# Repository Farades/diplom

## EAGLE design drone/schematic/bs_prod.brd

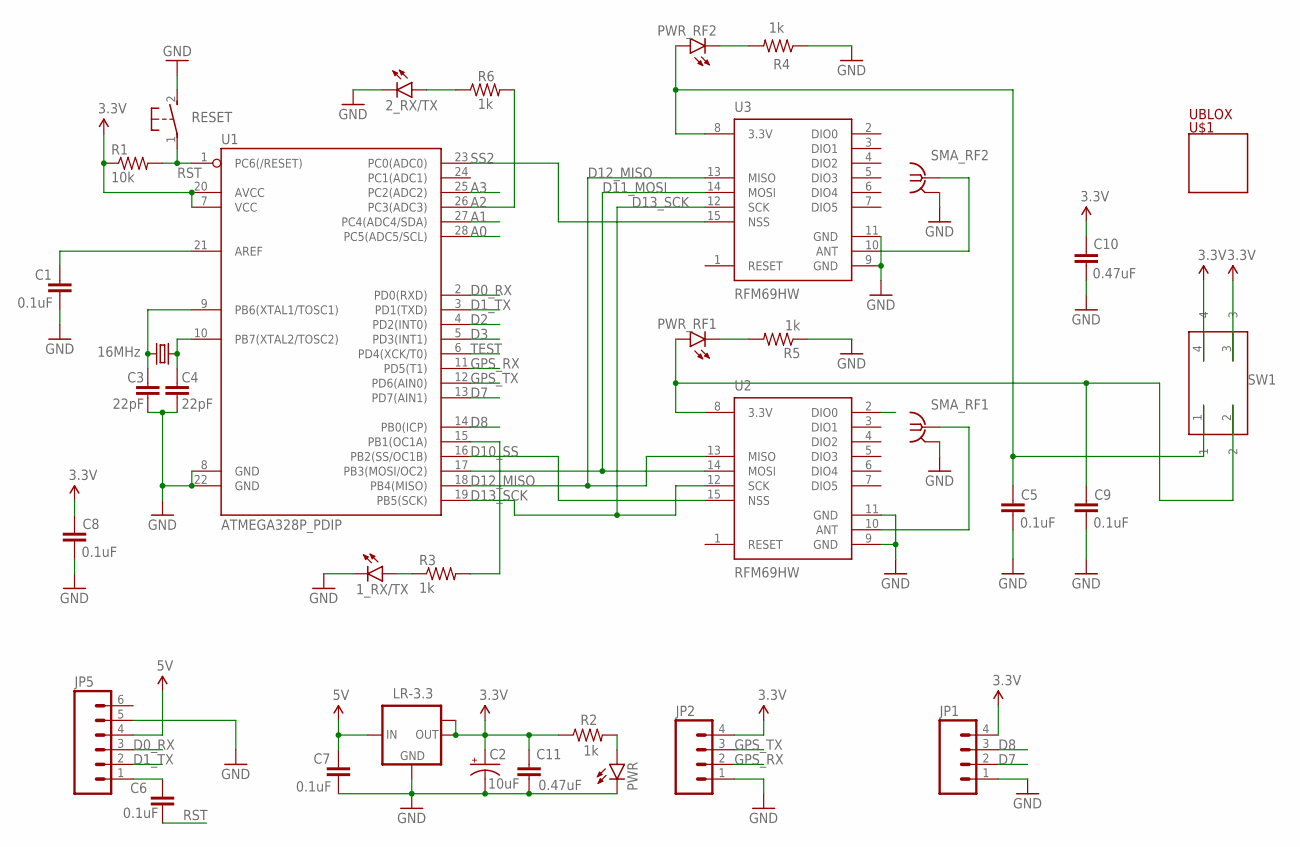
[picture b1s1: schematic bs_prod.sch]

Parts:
1_RX/TX, 2_RX/TX: LED1206; LED-1206
C1, C5, C6, C7, C8, C9: 0.1uF; 1206
C2: 10uF; PANASONIC_C
C3, C4: 22pF; 1206
C10, C11: 0.47uF; 1206
JP1, JP2: M04PTH; 1X04
JP5: M06SIP; 1X06
LR-3.3: LM1117IMPX-3.3; SOT223
PWR: LED1206; LED-1206
PWR_RF1, PWR_RF2: LED1206; LED-1206
R1: 10k; 1206
R2, R3, R4, R5, R6: 1k; 1206
RESET: DTSM-3
SMA_RF1, SMA_RF2: BU-SMC-V
SW1: 418117270902
U1: ATMEGA328P_PDIP; DIL28-3
U2, U3: RFM69HW; RFM69W-XXXS2
U$1: UBLOX
Y1: 16MHz; HC49UP

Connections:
3.3V: C2.+, C8.1, C10.1, C11.1, JP1.4, JP2.4, LR-3.3.2 (OUT), LR-3.3.TAB (OUT1), R1.1, R2.1, SW1.3, SW1.4, U1.7 (VCC), U1.20 (AVCC)
5V: C7.1, JP5.4, LR-3.3.3 (IN)
A0: U1.28 (PC5(ADC5/SCL))
A1: U1.27 (PC4(ADC4/SDA))
A2: R6.2, U1.26 (PC3(ADC3))
A3: U1.25 (PC2(ADC2))
D0_RX: JP5.3, U1.2 (PD0(RXD))
D1_TX: JP5.2, U1.3 (PD1(TXD))
D3: U1.5 (PD3(INT1))
D7: JP1.2, U1.13 (PD7(AIN1))
D8: JP1.3, U1.14 (PB0(ICP))
D10_SS: U1.16 (PB2(SS/OC1B)), U2.15 (NSS)
D11_MOSI: U1.17 (PB3(MOSI/OC2)), U2.14 (MOSI), U3.14 (MOSI)
D12_MISO: U1.18 (PB4(MISO)), U2.13 (MISO), U3.13 (MISO)
D13_SCK: U1.19 (PB5(SCK)), U2.12 (SCK), U3.12 (SCK)
GND: 1_RX/TX.C, 2_RX/TX.C, C1.2, C2.-, C3.2, C4.2, C5.2, C7.2, C8.2, C9.2, C10.2, C11.2, JP1.1, JP2.1, JP5.5, LR-3.3.1 (GND), PWR.C, R4.1, R5.1, RESET.2, SMA_RF1.2, SMA_RF1.3 (2), SMA_RF1.4 (2), SMA_RF1.5 (2), SMA_RF2.2, SMA_RF2.3 (2), SMA_RF2.4 (2), SMA_RF2.5 (2), U1.8 (GND), U1.22 (GND), U2.9 (GND), U2.11 (GND), U3.9 (GND), U3.11 (GND)
GPS_RX: JP2.2, U1.11 (PD5(T1))
GPS_TX: JP2.3, U1.12 (PD6(AIN0))
unnamed: PWR.A, R2.2
unnamed: C3.1, U1.9 (PB6(XTAL1/TOSC1)), Y1.2
unnamed: C4.1, U1.10 (PB7(XTAL2/TOSC2)), Y1.1
unnamed: SMA_RF1.1, U2.10 (ANT)
unnamed: PWR_RF2.C, R4.2
unnamed: C6.1, JP5.1
unnamed: 1_RX/TX.A, R3.1
unnamed: 2_RX/TX.A, R6.1
unnamed: C1.1, U1.21 (AREF)
unnamed: R3.2, U1.15 (PB1(OC1A))
unnamed: C5.1, PWR_RF2.A, SW1.1, U3.8 (3.3V)
unnamed: PWR_RF1.C, R5.2
unnamed: C9.1, PWR_RF1.A, SW1.2, U2.8 (3.3V)
unnamed: SMA_RF2.1, U3.10 (ANT)
RST: C6.2, R1.2, RESET.1, U1.1 (PC6(/RESET))
SS2: U1.23 (PC0(ADC0)), U3.15 (NSS)
TEST: U1.6 (PD4(XCK/T0))

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
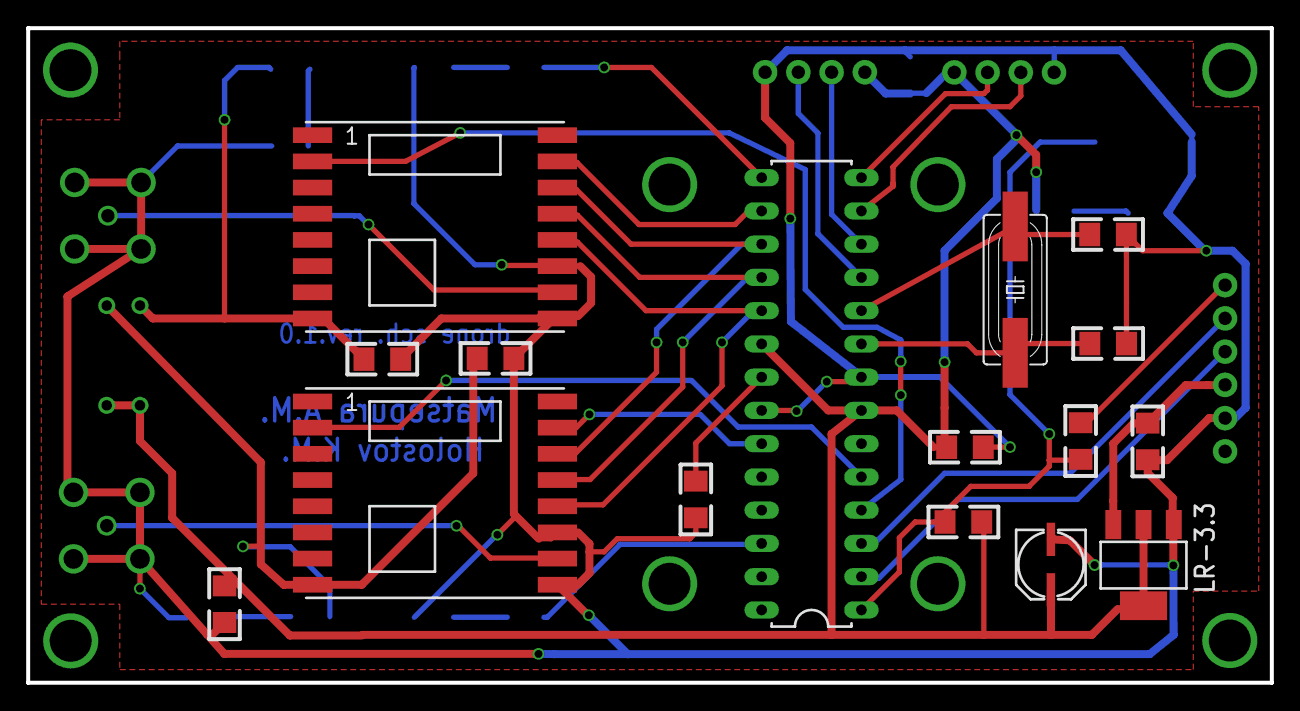
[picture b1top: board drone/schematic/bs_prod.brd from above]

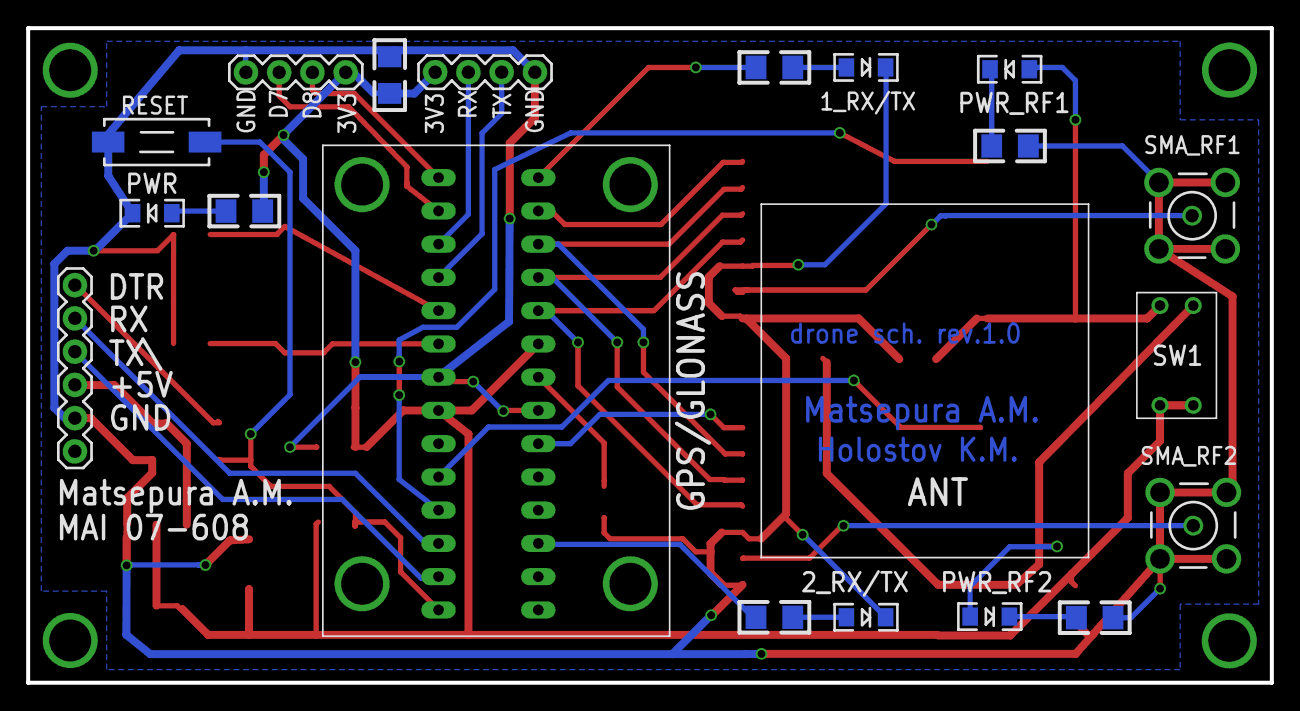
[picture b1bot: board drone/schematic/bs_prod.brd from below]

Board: 2 copper layers, 95.0 x 50.0 mm, 35 parts (19 on the bottom side), 31 nets.

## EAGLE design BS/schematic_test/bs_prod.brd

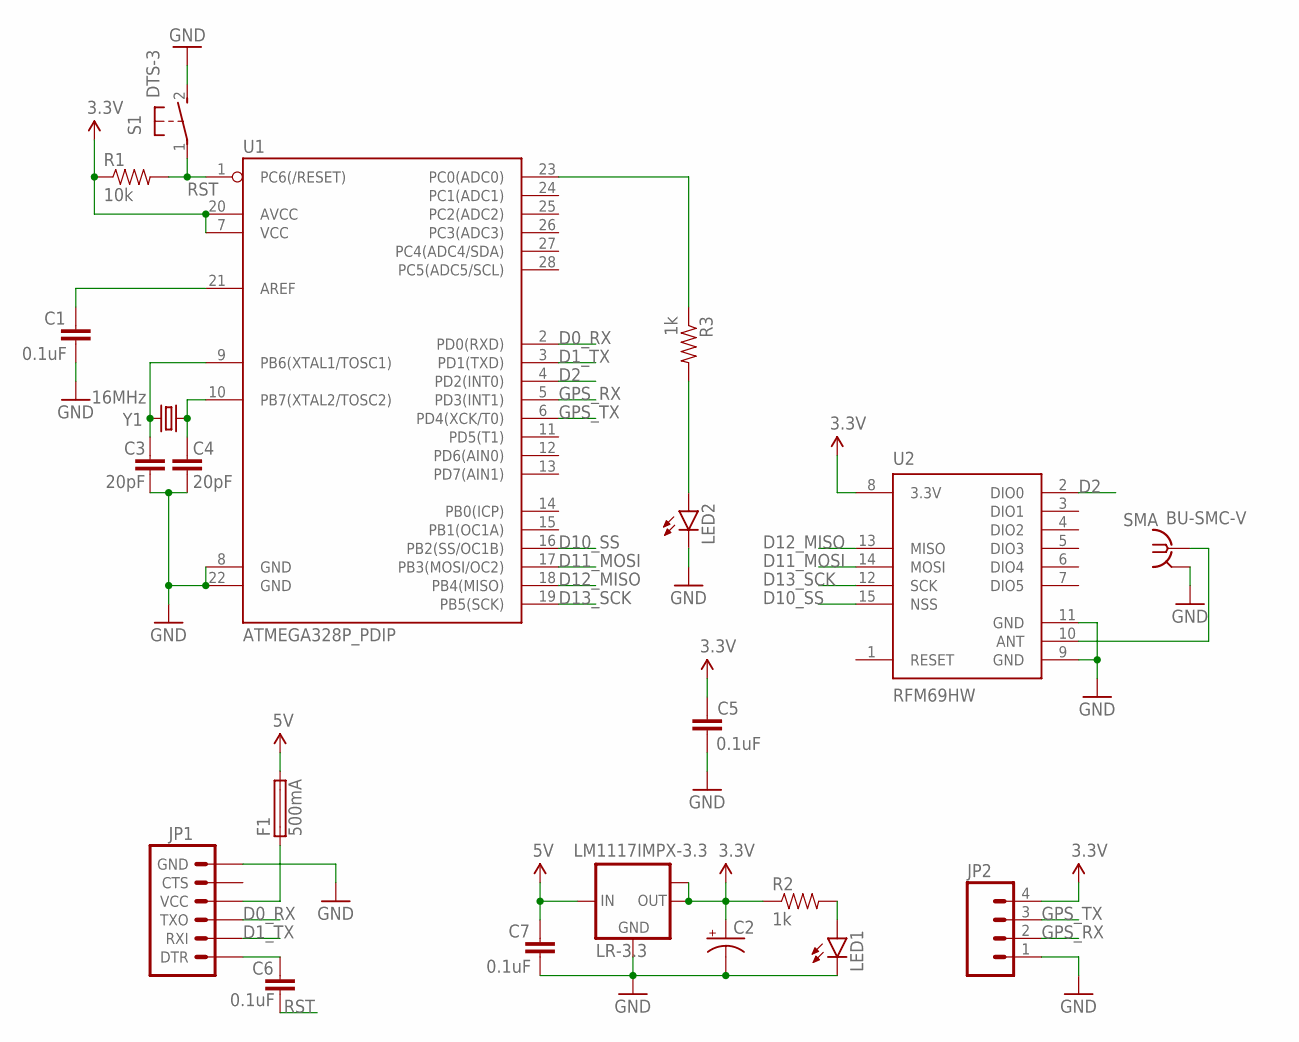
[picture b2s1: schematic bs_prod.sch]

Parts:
C1, C5, C6, C7: 0.1uF; 1206
C2: CAP_POLC; PANASONIC_C
C3, C4: 20pF; 1206
F1: 500mA; TE5
JP1: ARDUINO_SERIAL_PROGRAMPTH; 1X06
JP2: M04PTH; 1X04
LED1, LED2: LED1206; LED-1206
LR-3.3: LM1117IMPX-3.3; SOT223
R1: 10k; 1206
R2, R3: 1k; 1206
S1: DTS-3
SMA: BU-SMC-V
U1: ATMEGA328P_PDIP; DIL28-3
U2: RFM69HW; RFM69W-XXXS2
Y1: 16MHz; HC49UP

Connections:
3.3V: C2.+, C5.1, JP2.4, LR-3.3.2 (OUT), LR-3.3.TAB (OUT1), R1.1, R2.1, U1.7 (VCC), U1.20 (AVCC), U2.8 (3.3V)
5V: C7.1, F1.2, LR-3.3.3 (IN)
D0_RX: JP1.3 (TXO), U1.2 (PD0(RXD))
D1_TX: JP1.2 (RXI), U1.3 (PD1(TXD))
D2: U1.4 (PD2(INT0)), U2.2 (DIO0)
D10_SS: U1.16 (PB2(SS/OC1B)), U2.15 (NSS)
D11_MOSI: U1.17 (PB3(MOSI/OC2)), U2.14 (MOSI)
D12_MISO: U1.18 (PB4(MISO)), U2.13 (MISO)
D13_SCK: U1.19 (PB5(SCK)), U2.12 (SCK)
GND: C1.2, C2.-, C3.2, C4.2, C5.2, C7.2, JP1.6 (GND), JP2.1, LED1.C, LED2.C, LR-3.3.1 (GND), S1.2, SMA.2, SMA.3 (2), SMA.4 (2), SMA.5 (2), U1.8 (GND), U1.22 (GND), U2.9 (GND), U2.11 (GND)
GPS_RX: JP2.2, U1.5 (PD3(INT1))
GPS_TX: JP2.3, U1.6 (PD4(XCK/T0))
unnamed: LED1.A, R2.2
unnamed: C3.1, U1.9 (PB6(XTAL1/TOSC1)), Y1.2
unnamed: C4.1, U1.10 (PB7(XTAL2/TOSC2)), Y1.1
unnamed: SMA.1, U2.10 (ANT)
unnamed: F1.1, JP1.4 (VCC)
unnamed: C6.1, JP1.1 (DTR)
unnamed: R3.1, U1.23 (PC0(ADC0))
unnamed: LED2.A, R3.2
unnamed: C1.1, U1.21 (AREF)
RST: C6.2, R1.2, S1.1, U1.1 (PC6(/RESET))

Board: 2 copper layers, 21 parts (8 on the bottom side), 22 nets, no tracks yet.

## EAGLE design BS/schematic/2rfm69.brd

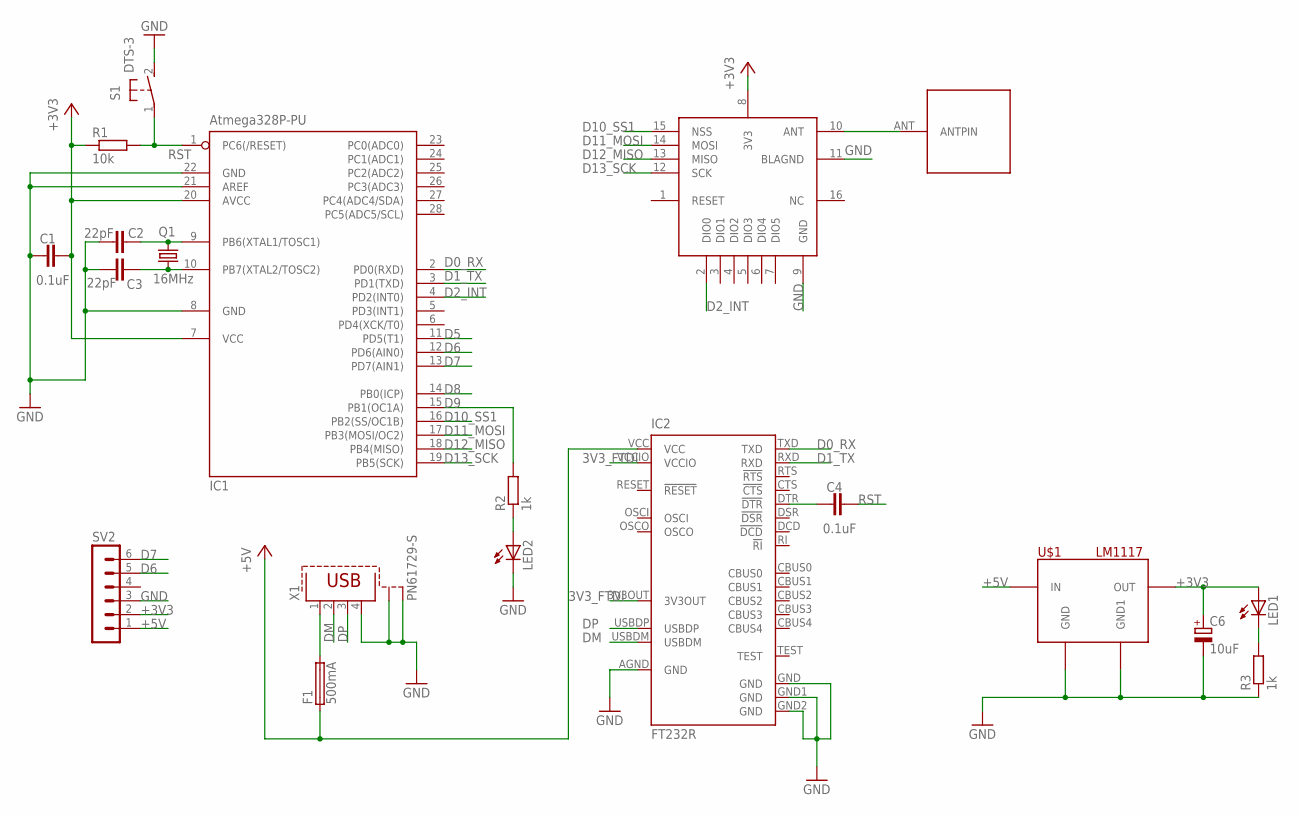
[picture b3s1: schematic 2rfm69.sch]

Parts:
C1, C4: 0.1uF; C050-025X075
C2, C3: 22pF; C050-025X075
C6: 10uF; E2,5-6E
F1: 500mA; TE5
IC1: Atmega328P-PU; DIL28-3
IC2: FT232R; DIL28-6
LED1, LED2: LED3MM
Q1: 16MHz; HC49/S
R1: 10k; 0204/7
R2, R3: 1k; 0204/7
S1: DTS-3
SV2: MA06-1
U1: RFM69
U$1: LM1117; SOT223
U$2: ANT
X1: PN61729-S

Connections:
3V3_FTDI: IC2.3V3OUT, IC2.VCCIO
+3V3: C1.2, C6.+, IC1.7 (VCC), IC1.20 (AVCC), LED1.A, R1.1, SV2.2, U1.8 (3V3), U$1.VOUT (OUT)
+5V: F1.1, IC2.VCC, SV2.1, U$1.VIN (IN)
D0_RX: IC1.2 (PD0(RXD)), IC2.TXD
D1_TX: IC1.3 (PD1(TXD)), IC2.RXD
D2_INT: IC1.4 (PD2(INT0)), U1.2 (DIO0)
D5: IC1.11 (PD5(T1))
D6: IC1.12 (PD6(AIN0)), SV2.5
D7: IC1.13 (PD7(AIN1)), SV2.6
D8: IC1.14 (PB0(ICP))
D9: IC1.15 (PB1(OC1A)), R2.2
D10_SS1: IC1.16 (PB2(SS/OC1B)), U1.15 (NSS)
D11_MOSI: IC1.17 (PB3(MOSI/OC2)), U1.14 (MOSI)
D12_MISO: IC1.18 (PB4(MISO)), U1.13 (MISO)
D13_SCK: IC1.19 (PB5(SCK)), U1.12 (SCK)
DM: IC2.USBDM, X1.2
DP: IC2.USBDP, X1.3
GND: C1.1, C2.1, C3.1, C6.-, IC1.8 (GND), IC1.21 (AREF), IC1.22 (GND), IC2.AGND (GND), IC2.GND, IC2.GND1 (GND), IC2.GND2 (GND), LED2.K (C), R3.1, S1.2, SV2.3, U1.9 (GND), U1.11 (BLAGND), U$1.GND, U$1.GND1, X1.4, X1.S1, X1.S2
unnamed: C2.2, IC1.9 (PB6(XTAL1/TOSC1)), Q1.1
unnamed: C3.2, IC1.10 (PB7(XTAL2/TOSC2)), Q1.2
unnamed: C4.1, IC2.DTR (!DTR)
unnamed: U1.10 (ANT), U$2.ANT
unnamed: LED1.K (C), R3.2
unnamed: LED2.A, R2.1
unnamed: F1.2, X1.1
RST: C4.2, IC1.1 (PC6(/RESET)), R1.2, S1.1

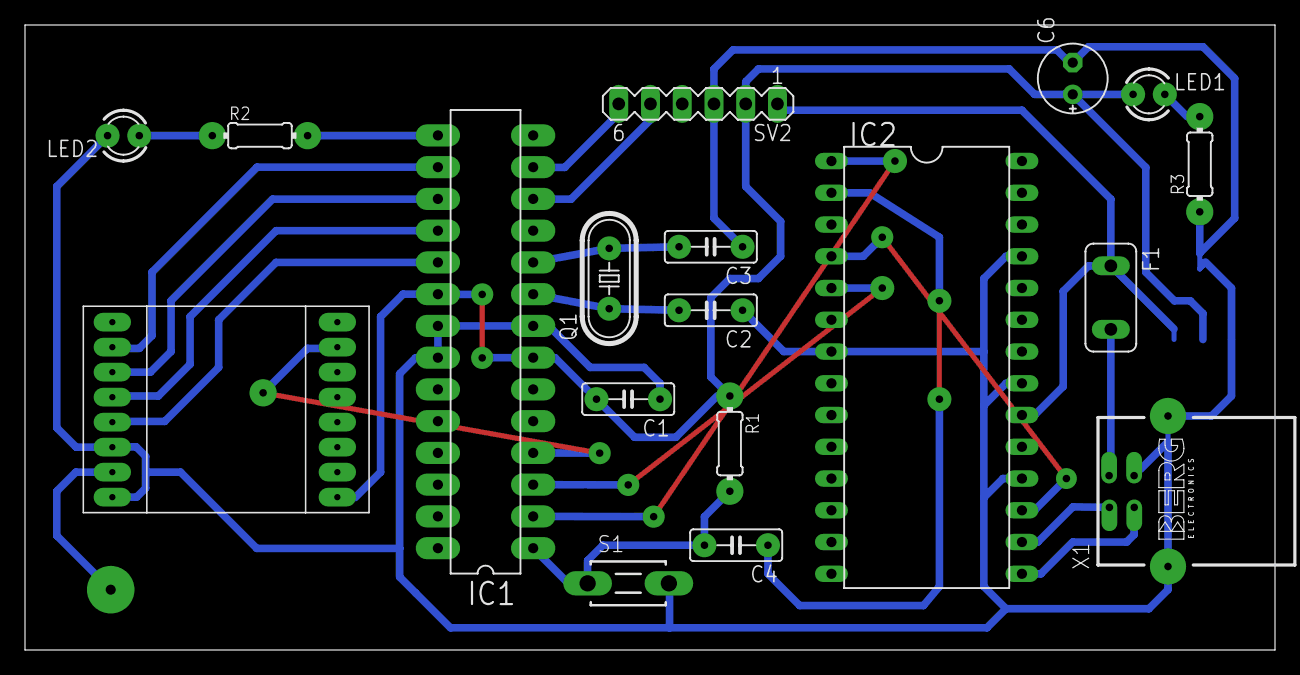
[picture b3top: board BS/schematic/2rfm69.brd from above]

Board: 2 copper layers, 100.0 x 50.0 mm, 20 parts (1 on the bottom side), 24 nets.

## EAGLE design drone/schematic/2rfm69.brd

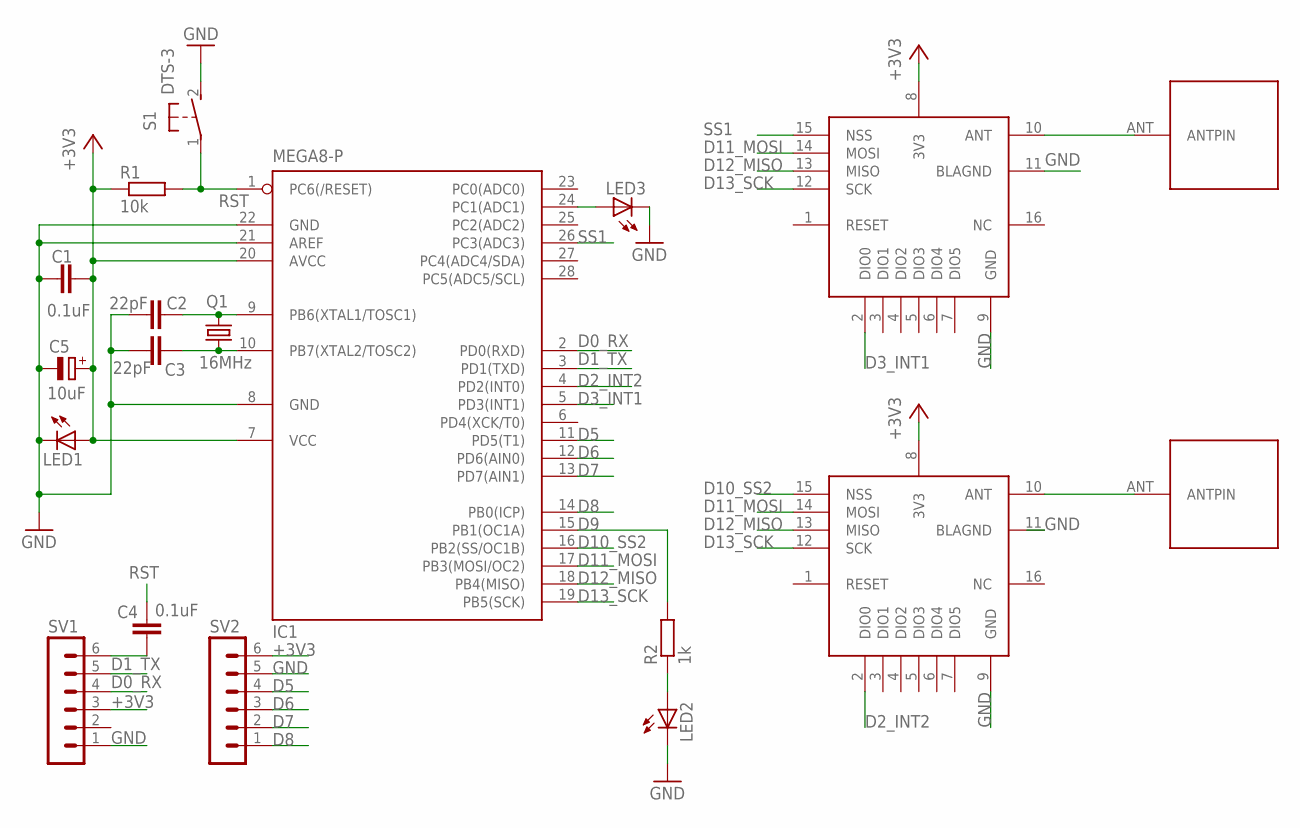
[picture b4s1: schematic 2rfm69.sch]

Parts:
C1, C4: 0.1uF; C050-025X075
C2, C3: 22pF; C050-025X075
C5: 10uF; E2,5-6
IC1: MEGA8-P; DIL28-3
LED1, LED2, LED3: LED3MM
Q1: 16MHz; HC49/S
R1: 10k; 0204/7
R2: 1k; 0204/7
S1: DTS-3
SV1, SV2: MA06-1
U1, U2: RFM692; RFM69
U$1, U$2: ANT

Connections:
+3V3: C1.2, C5.+, IC1.7 (VCC), IC1.20 (AVCC), LED1.A, R1.1, SV1.3, SV2.6, U1.8 (3V3), U2.8 (3V3)
D0_RX: IC1.2 (PD0(RXD)), SV1.4
D1_TX: IC1.3 (PD1(TXD)), SV1.5
D2_INT2: IC1.4 (PD2(INT0)), U2.2 (DIO0)
D3_INT1: IC1.5 (PD3(INT1)), U1.2 (DIO0)
D5: IC1.11 (PD5(T1)), SV2.4
D6: IC1.12 (PD6(AIN0)), SV2.3
D7: IC1.13 (PD7(AIN1)), SV2.2
D8: IC1.14 (PB0(ICP)), SV2.1
D9: IC1.15 (PB1(OC1A)), R2.2
D10_SS2: IC1.16 (PB2(SS/OC1B)), U2.15 (NSS)
D11_MOSI: IC1.17 (PB3(MOSI/OC2)), U1.14 (MOSI), U2.14 (MOSI)
D12_MISO: IC1.18 (PB4(MISO)), U1.13 (MISO), U2.13 (MISO)
D13_SCK: IC1.19 (PB5(SCK)), U1.12 (SCK), U2.12 (SCK)
GND: C1.1, C2.1, C3.1, C5.-, IC1.8 (GND), IC1.21 (AREF), IC1.22 (GND), LED1.K (C), LED2.K (C), LED3.K (C), S1.2, SV1.1, SV2.5, U1.9 (GND), U1.11 (BLAGND), U2.9 (GND), U2.11 (BLAGND)
unnamed: C2.2, IC1.9 (PB6(XTAL1/TOSC1)), Q1.1
unnamed: C3.2, IC1.10 (PB7(XTAL2/TOSC2)), Q1.2
unnamed: C4.1, SV1.6
unnamed: U1.10 (ANT), U$2.ANT
unnamed: U2.10 (ANT), U$1.ANT
unnamed: LED2.A, R2.1
unnamed: IC1.24 (PC1(ADC1)), LED3.A
RST: C4.2, IC1.1 (PC6(/RESET)), R1.2, S1.1
SS1: IC1.26 (PC3(ADC3)), U1.15 (NSS)

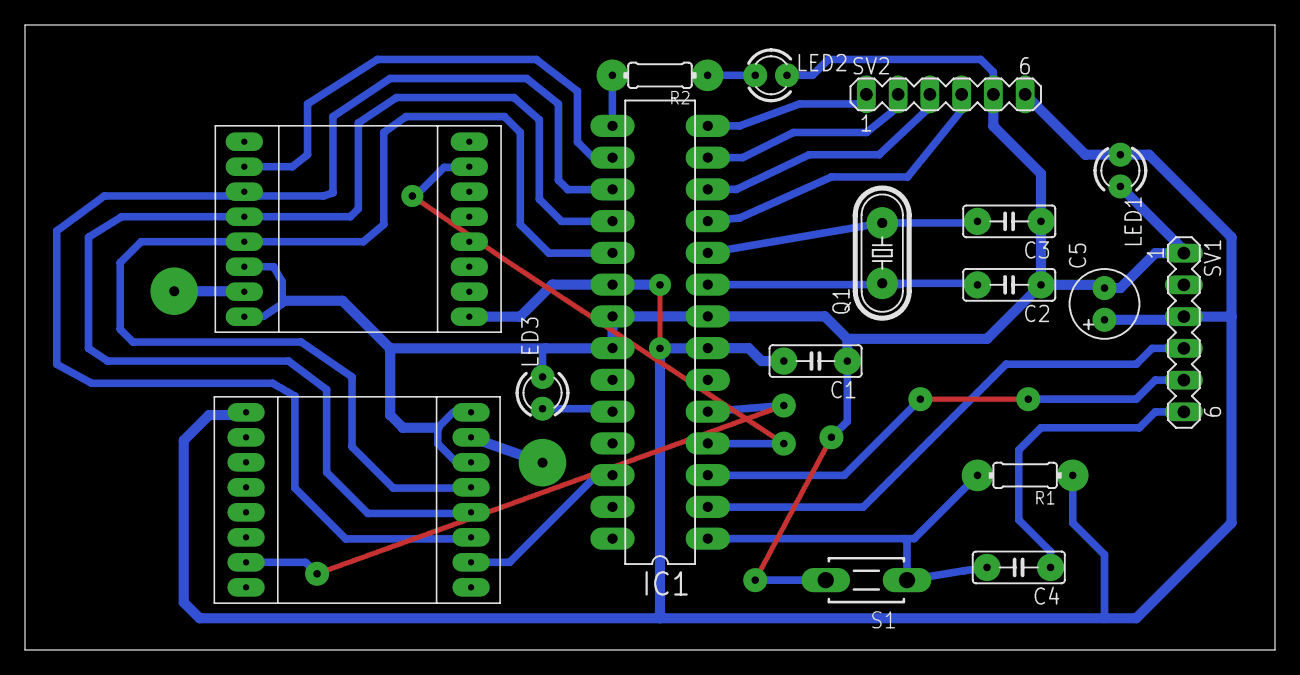
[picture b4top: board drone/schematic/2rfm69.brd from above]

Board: 2 copper layers, 100.0 x 50.0 mm, 19 parts (0 on the bottom side), 24 nets.

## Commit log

2014-09-03 krylov add
2014-09-03 add book
2014-09-09 add RFM69
2014-09-09 add first version schematic drone
2014-09-10 some fixes
2014-09-10 schematic drone
2014-09-11 test drone DIP schematic complete
2014-09-11 change via's diametr in capacictor's
2014-09-12 manager app create, terminal rx done
2014-09-15 add terminal send
2014-09-15 deleted compile file
2014-09-15 arduino parser
2014-09-16 add test firmware
2014-10-28 add bs schenatic
2014-10-29 Test schematic BS
2014-11-07 add minimal schematic prod and PZ
2014-11-13 add OT and OS part
2014-11-16 BS schematic prod test add
2014-11-17 BS schematic prod
2014-11-18 add polygon to BS schematic
2014-11-19 final BS schematic
2014-11-21 add minimal economic part
2014-11-23 economy part
2014-12-03 some fixed econom part
2014-12-07 final econom part
2014-12-07 add drone schematic
2014-12-08 production drone schematic
2014-12-10 some fixed for drone schematic
2014-12-11 add main layout
2014-12-24 add task for diplom
2015-01-06 minimal functional bs
2015-01-06 add minimal work drone
2015-01-10 some fixed
2015-01-11 add blanks
2015-01-11 add java manager
2015-01-11 work comport
2015-01-11 broadcast message from bs to group
2015-01-11 some change
2015-01-12 some fixed PZ
2015-01-12 current drone schematic
2015-01-12 add drone and bs board model
2015-01-15 Manager assembly receive string
2015-01-15 com & drones update observer
2015-01-15 manager: tabpane, droneslist, minimal terminalPanel
2015-01-15 refactoring DroneListPanel -> DroneTablePanel
2015-01-16 add sendText in Terminal
2015-01-16 last update in status bar
2015-01-17 add dronePanel
2015-01-17 logging every drone states
2015-01-17 sending command to drone add
2015-01-18 interview all drones & get data to comport
2015-01-18 base station - analyze two drone (minimal)
2015-01-19 add pmo bs to pz
2015-01-19 add pmo drone to pz
2015-01-19 deleted .do file
2015-01-19 deleted old_terminal
2015-01-19 refactoring location file's
2015-01-22 add uml diagram to evm pmo
2015-01-22 some fixed in presentation
2015-01-25 add energy efficiency & secretiveness
2015-01-25 final diplom pz
2015-01-27 final version

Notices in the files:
parts and their libraries:
SparkFun-DigitalIC: Licensing: Creative Commons ShareAlike 4.0 International - https://creativecommons.org/licenses/by-sa/4.0
Eagle_Wuerth_Elektronik_Switch: Copyright: Würth Elektronik
